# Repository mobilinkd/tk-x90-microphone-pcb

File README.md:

# Kenwood TK-x90 Microphone PCB

This directory contains the KiCad project for the Kenwood TK-x90 microphone
connector. This is designed to help convert a KMC-30 or KMC-32 with an RJ-45
connector to one that will work with th Kenwood TK-690, TK-790 and TK-890
radios.  It is intended to be used with the [TK-x90 Microphone Connector Housing](https://github.com/mobilinkd/tk-x90-mic-connector-housing).

<table>
  <tr>
    <td>  </td>
  </tr>
</table>

## License

This circuit design is licensed under the [CC-BY-SA](http://creativecommons.org/licenses/by-sa/4.0/).

Please attribute the work to *Rob Riggs, WX9O, Mobilinkd LLC*.

## Overview

This PCB is just a set of 8 through connections, with one end being solder cup
termination for the microphone wires and the other being mating sockets for
the pogo pins on the radio.

## BOM

<table>
  <tr>
    <td>  </td>
    <td>  </td>
  </tr>
</table>

 1. 8x [MillMax 310-13-101-41-001000](https://www.digikey.com/product-detail/en/mill-max-manufacturing-corp/310-13-101-41-001000/ED7464-01-ND/265808)

The MillMax parts are usually cheaper to order in longer strips.  They are
designed to fit IC leads, useful for making custom IC sockets.  Rather than
just buying eight, consider buying one or more [strips of 64](https://www.digikey.com/products/en?keywords=310-13-164-41-001000).
If you intend to make the programmer adapter, you will need 2 more.

These pins have a habit of breaking when being cut from the strip, so
be sure to buy extra to account for some wastage.

## Assembly

Using a 3D printer, print the 4 components of the housing.  It is important
when printing the alignment jig that the printer does not over-extrude or
cause holes to be smaller than they should be.  Each square on the jig should
be 2.7mm square.

Place 8 of the Mill Max parts in the appropriate locations on the alignment
jig.  This may require some filing of the parts to ensure that they are
2.54mm square.  Add all 8 of the Mill Max parts in the jig, leaving the TRD
programming pin socket empty.  This is the one at the 7 o'clock position.

## Cable Assembly

These assembly instruction assume that you have the [connector components](../programmer-connector/README.md)
completed and partially assembled.

 1. Cut an the Ethernet cable to the desired length.
 1. Cut off any RJ-45 connectors that are attached at either end.
 1. Cut back about 10-15mm of the outer insulation from one end.
 1. Find the blue/white, orange, and the orange/white wires.
 1. Strip about 3-4mm of insulation from these three wires.
 1. Trim the remaining wires back to the outer insulation, leaving just
    these three exposed.
 1. Slide the shrink tubing onto the cable.
 1. Solder the blue/white wire to GND on the USB/serial board.
 1. Solder the orange wire to the TX line of the USB/serial board.
 1. Solder the orange/white wire to the RX line of the USB/serial board.
 
One half of the cable is complete.  Verify that the shrink tubing is on
cable.  We won't heat the shrink tubing until we verify the cable works.
 
We now turn our attention to the other end of the cable and the  PCB
that was assembled above.  Note that when soldering the serial wires,
we are **not crossing the TX/RX wires**.
 
Before we begin, there may be burrs or other protrusions on the PCB from
manufacturing.  These need to be filed off smooth so that the PCB will fit
in the connector base.  Clean up the PCB and verify that it will in the
base, but do not push it in so far that it engages the clips.  The board
diameter should measure 17mm.  There is only 0.5mm clearance for the PCB
designed into the connector assembly.
 
 1. Slide the connector shell/boot assembly over the end of the cable.
 1. Cut back about 15mm of the outer insulation from the remaining end.
 1. Find the blue/white, orange, and the orange/white wires.
 1. Strip about 3-4mm of insulation from these three wires.
 1. Trim the remaining wires back to the outer insulation, leaving just
    these three exposed.
 1. Solder the blue/white wire to GND on the PCB.
 1. Solder the orange wire to the TX line of the PCB.
 1. Solder the orange/white wire to the RX line of PCB.

The cable ends have been soldered.  We are now going to mount the PCB
in the connector base and verify that the cable works.

 1. Orient the PCB so that the two MillMax sockets are near the screw
    attachement point of the base.
 1. Find the clips and align the slots on the PCB with the clips.
 1. Push the PCB into the base until the clips engage.
 
Now we need to test the programmer cable.  I recommend going through the
full read and write process with the Kenwood programming software.
Information on how to do that is outside the scope of this brief
document.

In a pinch we can just watch the traffic come through as the radio
boots up, testing reading only.  This is what we will do here.

A word of warning/advice.  Do not connect or disconnect the cable
with the radio on.  Do not power on the radio if the cable is connected
to the radio but not plugged in to a USB port.

 1. Ensure the radio is powered off.
 1. Connect the serial adapter to a computer.
 1. Connect the adapter to the radio, aligning the connector base with the
    PCB carefully and screwing in the connector to ensure that it is
    properly secured.
 1. Open a serial console (such as PuTTY or CuteCom)
 1. Set the serial parameters to 9600 baud, 8N1.
 1. Open the serial port.
 1. Turn on the radio.
 1. You should see a bunch of binary data flow into the terminal
 1. Turn the channel select knob on the radio.  You should see data being
    emitted for each click of the knob.

If this test failed, go back and verify all of the connections.  Verify
that the USB/Serial adapter did not reverse the TX/RX designation on the
adapter board.  (That has bitten me more than once.)

Assuming it passed, we need to finish the assembly.

 1. Turn the radio off.
 1. Disconnect the cable from the radio.
 1. Unplug the USB serial adapter.
 1. Use the shink tubing or electrical tape to protect the connection to
    the USB Serial adapter.
 1. Slide the connector boot assembly down towards the base.
 1. Orient the boot assembly so the cutouts line up with the clips holding
    the PCB in place.  This should also orient the clips on the shell with
    the cutouts on the base.
 1. Insert the shell into the base, pressing until the clips lock in place.
    This may require some force.

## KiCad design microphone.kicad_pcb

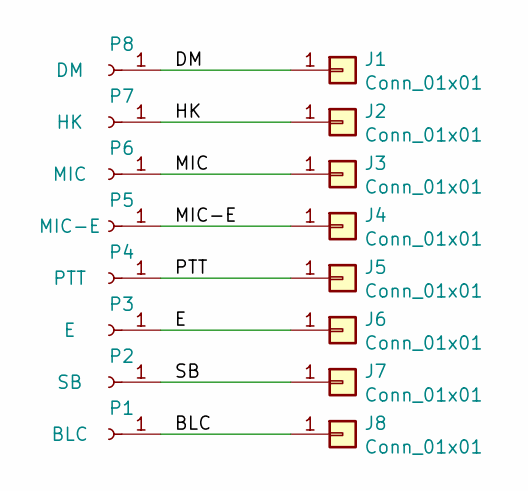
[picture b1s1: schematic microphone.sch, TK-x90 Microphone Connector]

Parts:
J1, J2, J3, J4, J5, J6, J7, J8: Conn_01x01; SolderWire-0.1sqmm_1x01_D0.4mm_OD1mm
P1: BLC; MillMax329SolderCup
P2: SB; MillMax329SolderCup
P3: E; MillMax329SolderCup
P4: PTT; MillMax329SolderCup
P5: MIC-E; MillMax329SolderCup
P6: MIC; MillMax329SolderCup
P7: HK; MillMax329SolderCup
P8: DM; MillMax329SolderCup

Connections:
/BLC: J8.1, P1.1
/DM: J1.1, P8.1
/E: J6.1, P3.1
/HK: J2.1, P7.1
/MIC: J3.1, P6.1
/MIC-E: J4.1, P5.1
/PTT: J5.1, P4.1
/SB: J7.1, P2.1

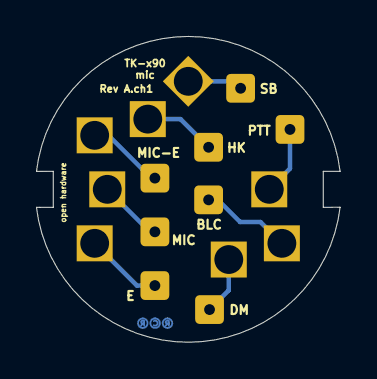
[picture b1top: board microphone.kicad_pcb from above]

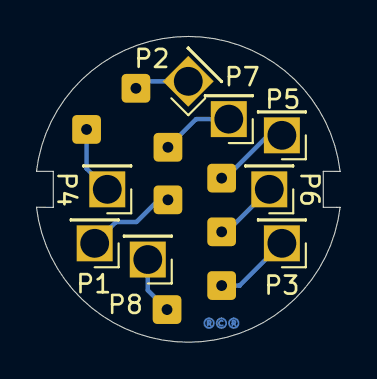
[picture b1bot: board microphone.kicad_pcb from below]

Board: 2 copper layers, 16.9 x 17.0 mm, 16 parts (8 on the bottom side), 8 nets.

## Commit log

2020-07-27 Initial commit.
2021-02-11 Adds wirepads.

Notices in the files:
microphone.kicad_pcb:
CC BY-SA 4.0
© 2020 Mobilinkd LLC
microphone.sch:
https://creativecommons.org/licenses/by-sa/4.0
